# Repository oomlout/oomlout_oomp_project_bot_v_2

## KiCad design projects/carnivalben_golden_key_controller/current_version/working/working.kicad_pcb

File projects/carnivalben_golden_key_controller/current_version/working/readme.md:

# golden_key
 
## summary 
* id: carnivalben_golden_key_controller
* user: carnivalben
* name: golden_key
* board: controller
* repo: https://github.com/CarnivalBen/golden-key
* src_file_repo_kicad_pcb: controller/pcb/controller.kicad_pcb
* src_file_repo_kicad_pcb_link: https://github.com/CarnivalBen/golden-key/tree/master/controller/pcb/controller.kicad_pcb

* src_file_repo_sch: controller/pcb/controller.sch
* src_file_repo_sch_link: https://github.com/CarnivalBen/golden-key/tree/master/controller/pcb/controller.sch
* full details link: https://github.com/oomlout/oomlout_oomp_project_bot_v_2/tree/main/projects/carnivalben_golden_key_controller/current_version/working  

## schematic  
  
[schematic (pdf)](working_schematic.pdf) 

## pcb  

[board (pdf)](working.pdf)  

## working_bom
| Id | Designator | Footprint | Quantity | Designation | Supplier and ref |  | None | 
| --- | --- | --- | --- | --- | --- | --- | --- | 
| 1 | C5,C1,C3 | C_Disc_D3.0mm_W1.6mm_P2.50mm | 3 | 10nF |  |  | [''] | 
| 2 | D1,D17,D10,D12,D15 | LED_D5.0mm | 5 | WHITE |  |  | [''] | 
| 3 | D3 | LED_D5.0mm | 1 | W REV3 |  |  | [''] | 
| 4 | D4 | LED_D5.0mm | 1 | W REV2 |  |  | [''] | 
| 5 | D5 | LED_D5.0mm | 1 | W REV1 |  |  | [''] | 
| 6 | D6 | LED_D5.0mm | 1 | W FWD1 |  |  | [''] | 
| 7 | D7 | LED_D5.0mm | 1 | W FWD2 |  |  | [''] | 
| 8 | D8 | LED_D5.0mm | 1 | W FWD3 |  |  | [''] | 
| 9 | D9,D13,D14,D11 | D_A-405_P7.62mm_Horizontal | 4 | 1N4001 |  |  | [''] | 
| 10 | Q2,Q3 | TO-220-3_Horizontal | 2 | TIP32 |  |  | [''] | 
| 11 | Q4,Q5,Q15 | TO-92_Inline_Wide | 3 | 2N2222 |  |  | [''] | 
| 12 | Q12,Q13 | TO-220-3_Horizontal | 2 | TIP31 |  |  | [''] | 
| 13 | R2,R15,R16,R18,R19,R20,R27,R17 | R_Axial_DIN0411_L9.9mm_D3.6mm_P12.70mm_Horizontal | 8 | 330R |  |  | [''] | 
| 14 | R3,R1 | R_Axial_DIN0411_L9.9mm_D3.6mm_P12.70mm_Horizontal | 2 | 165R |  |  | [''] | 
| 15 | R11,R12 | R_Axial_DIN0411_L9.9mm_D3.6mm_P12.70mm_Horizontal | 2 | 100R |  |  | [''] | 
| 16 | R25 | R_Axial_DIN0411_L9.9mm_D3.6mm_P12.70mm_Horizontal | 1 | 1K |  |  | [''] | 
| 17 | U1 | TO-220-3_Horizontal | 1 | LM78M05 |  |  | [''] | 
| 18 | U2 | DIP-8_W7.62mm_Socket_LongPads | 1 | PIC12F1501-ISN |  |  | [''] | 
| 19 | U3 | DIP-16_W7.62mm_Socket_LongPads | 1 | 74HC595 |  |  | [''] | 
| 20 | D2 | D_A-405_P7.62mm_Horizontal | 1 | 12v |  |  | [''] | 
| 21 | D16 | LED_D5.0mm | 1 | W STOP |  |  | [''] | 
| 22 | J2 | Potentiometer_WirePads_Small | 1 | 10K POT |  |  | [''] | 
| 23 | C4,C2 | CP_Radial_D6.3mm_P2.50mm | 2 | 400uF |  |  | [''] | 
| 24 | J1 | Barrier_Terminal_P8.27_1x4 | 1 | POWER |  |  | [''] | 
| 25 | J3 | Pin_Header_Straight_1x03_Pitch2.54mm | 1 | Gradient |  |  | [''] | 

## bom_schematic
| Ref | Qnty | Value | Cmp name | Footprint | Description | Vendor | DNP | 
| --- | --- | --- | --- | --- | --- | --- | --- | 
| C1, C3, C5 | 3 | 10nF | C | Capacitors_THT:C_Disc_D3.0mm_W1.6mm_P2.50mm | Unpolarized capacitor |  |  | 
| C2, C4 | 2 | 400uF | CP-Device | Capacitors_THT:CP_Radial_D6.3mm_P2.50mm |  |  |  | 
| D1, D10, D12, D15, D17 | 5 | WHITE | LED | LEDs:LED_D5.0mm | Light emitting diode |  |  | 
| D2 | 1 | 12v | D_Zener | Diodes_THT:D_A-405_P7.62mm_Horizontal | Zener diode |  |  | 
| D3 | 1 | W REV3 | LED | LEDs:LED_D5.0mm | Light emitting diode |  |  | 
| D4 | 1 | W REV2 | LED | LEDs:LED_D5.0mm | Light emitting diode |  |  | 
| D5 | 1 | W REV1 | LED | LEDs:LED_D5.0mm | Light emitting diode |  |  | 
| D6 | 1 | W FWD1 | LED | LEDs:LED_D5.0mm | Light emitting diode |  |  | 
| D7 | 1 | W FWD2 | LED | LEDs:LED_D5.0mm | Light emitting diode |  |  | 
| D8 | 1 | W FWD3 | LED | LEDs:LED_D5.0mm | Light emitting diode |  |  | 
| D9, D11, D13, D14 | 4 | 1N4001 | D | Diodes_THT:D_A-405_P7.62mm_Horizontal | Diode |  |  | 
| D16 | 1 | W STOP | LED | LEDs:LED_D5.0mm | Light emitting diode |  |  | 
| J1 | 1 | POWER | Conn_01x04 | carnivalben:Barrier_Terminal_P8.27_1x4 | Generic connector, single row, 01x04, script generated (kicad-library-utils/schlib/autogen/connector/) |  |  | 
| J2 | 1 | 10K POT | Conn_01x03 | Potentiometers:Potentiometer_WirePads_Small | Generic connector, single row, 01x03, script generated (kicad-library-utils/schlib/autogen/connector/) |  |  | 
| J3 | 1 | Gradient | Conn_01x03 | Pin_Headers:Pin_Header_Straight_1x03_Pitch2.54mm | Generic connector, single row, 01x03, script generated (kicad-library-utils/schlib/autogen/connector/) |  |  | 
| Q2, Q3 | 2 | TIP32 | TIP42 | TO_SOT_Packages_THT:TO-220-3_Horizontal | -6A Ic, -40V Vce, Power PNP Transistor, TO-220 |  |  | 
| Q4, Q5, Q15 | 3 | 2N2222 | BC237 | TO_SOT_Packages_THT:TO-92_Inline_Wide | 100mA Ic, 50V Vce, Epitaxial Silicon NPN Transistor, TO-92 |  |  | 
| Q12, Q13 | 2 | TIP31 | TIP41 | TO_SOT_Packages_THT:TO-220-3_Horizontal | 6A Ic, 40V Vce, Power NPN Transistor, TO-220 |  |  | 
| R1, R3 | 2 | 165R | R | Resistors_THT:R_Axial_DIN0411_L9.9mm_D3.6mm_P12.70mm_Horizontal | Resistor |  |  | 
| R2, R15, R16, R17, R18, R19, R20, R27 | 8 | 330R | R | Resistors_THT:R_Axial_DIN0411_L9.9mm_D3.6mm_P12.70mm_Horizontal | Resistor |  |  | 
| R11, R12 | 2 | 100R | R | Resistors_THT:R_Axial_DIN0411_L9.9mm_D3.6mm_P12.70mm_Horizontal | Resistor |  |  | 
| R25 | 1 | 1K | R | Resistors_THT:R_Axial_DIN0411_L9.9mm_D3.6mm_P12.70mm_Horizontal | Resistor |  |  | 
| U1 | 1 | LM78M05_TO220 | LM78M05_TO220 | TO_SOT_Packages_THT:TO-220-3_Horizontal | Positive 500mA 35V Linear Regulator, Fixed Output 5V, TO-220 |  |  | 
| U2 | 1 | PIC12F1501-ISN | PIC12F1501-ISN | Housings_DIP:DIP-8_W7.62mm_Socket_LongPads | PIC12F1501, 1024W FLASH, 64B SRAM, SO8 |  |  | 
| U3 | 1 | 74HC595 | 74HC595 | Housings_DIP:DIP-16_W7.62mm_Socket_LongPads | 8-bit serial in/out Shift Register 3-State Outputs |  |  |

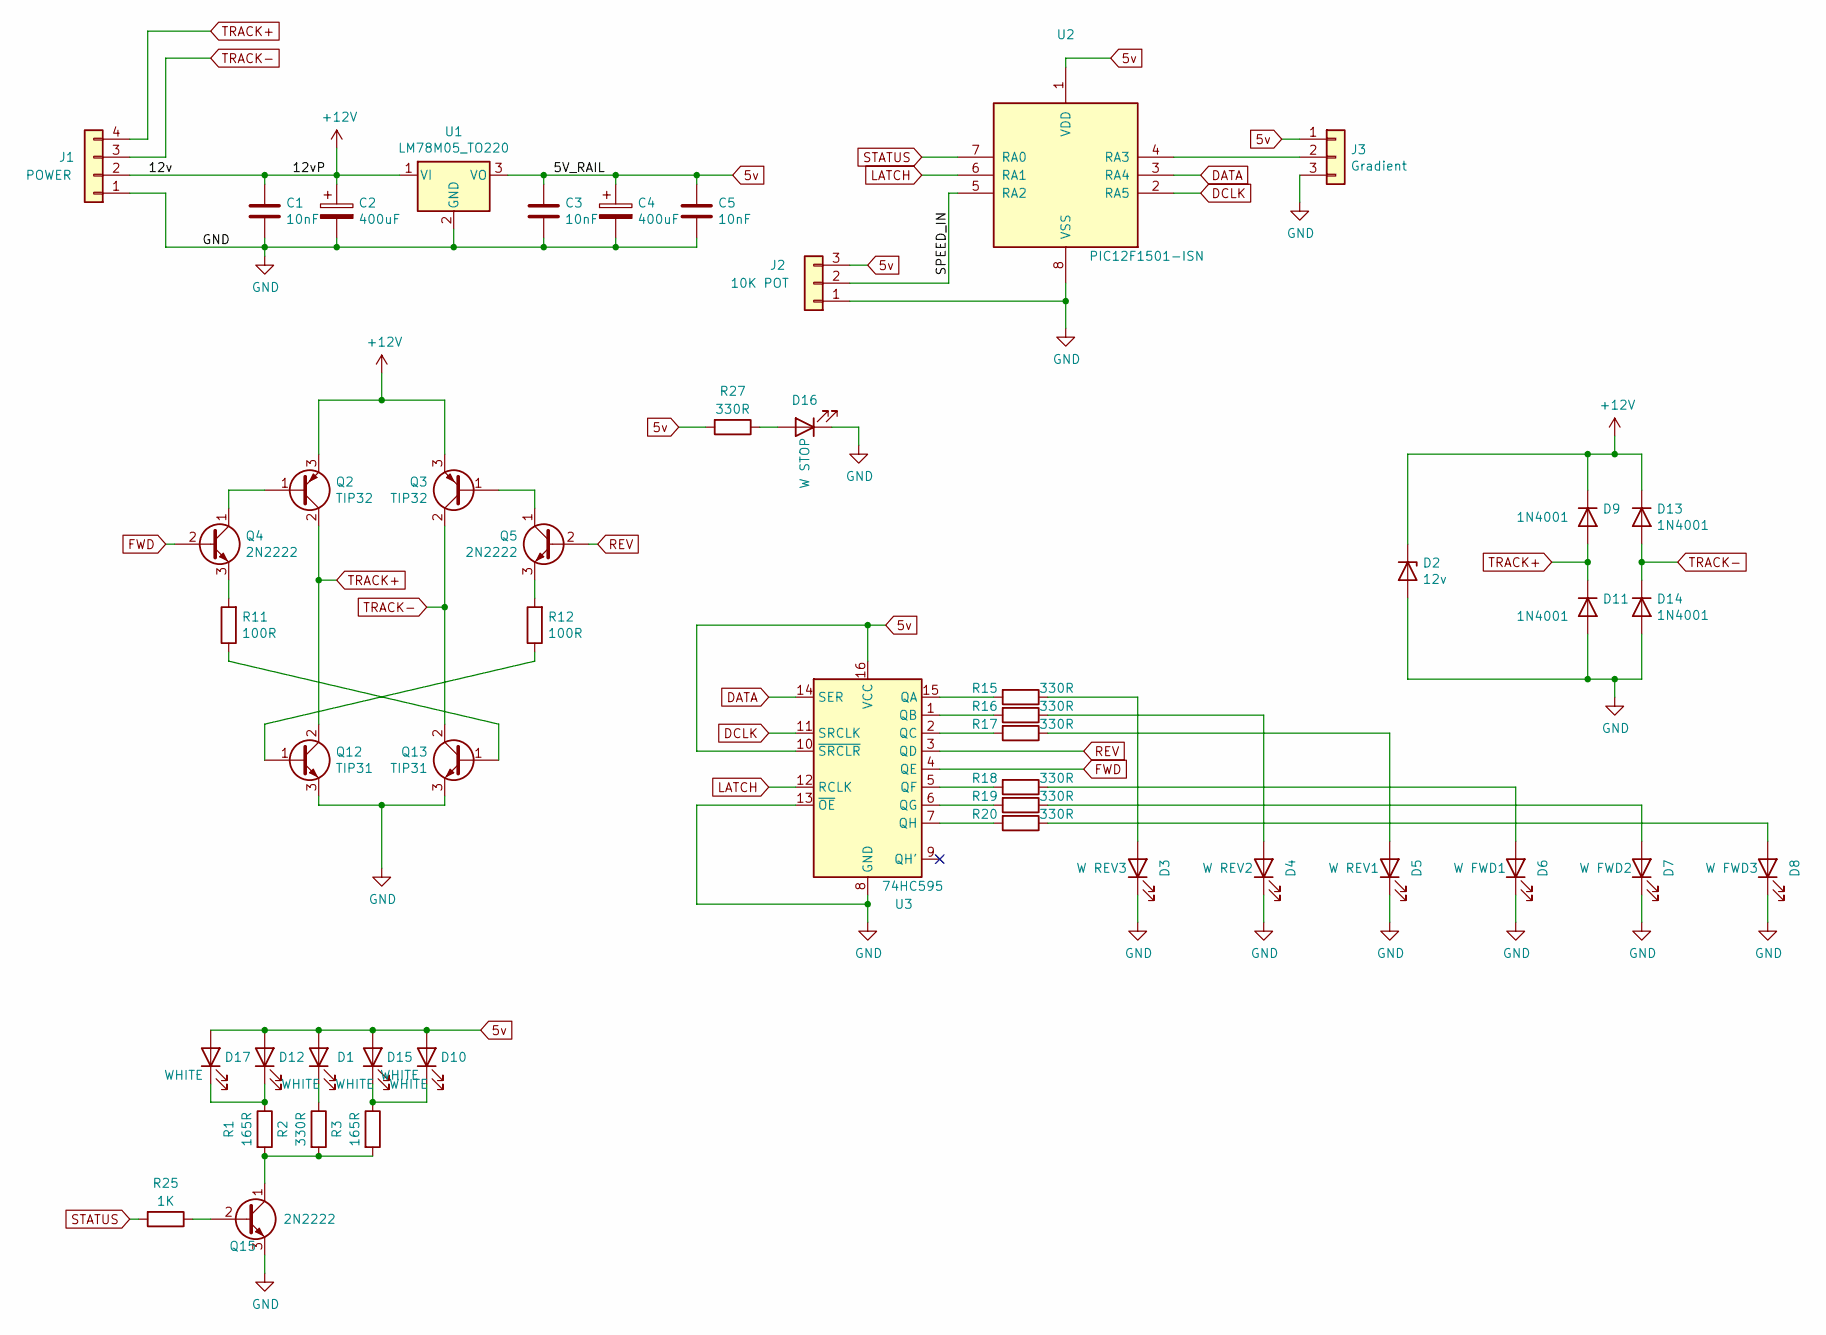
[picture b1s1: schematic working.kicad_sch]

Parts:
C1, C3, C5: 10nF; C_Disc_D3.0mm_W1.6mm_P2.50mm
C2, C4: 400uF; CP_Radial_D6.3mm_P2.50mm
D1, D10, D12, D15, D17: WHITE; LED_D5.0mm
D2: 12v; D_A-405_P7.62mm_Horizontal
D3: W REV3; LED_D5.0mm
D4: W REV2; LED_D5.0mm
D5: W REV1; LED_D5.0mm
D6: W FWD1; LED_D5.0mm
D7: W FWD2; LED_D5.0mm
D8: W FWD3; LED_D5.0mm
D9, D11, D13, D14: 1N4001; D_A-405_P7.62mm_Horizontal
D16: W STOP; LED_D5.0mm
J1: POWER; Barrier_Terminal_P8.27_1x4
J2: 10K POT; Potentiometer_WirePads_Small
J3: Gradient; Pin_Header_Straight_1x03_Pitch2.54mm
Q2, Q3: TIP32; TO-220-3_Horizontal
Q4, Q5, Q15: 2N2222; TO-92_Inline_Wide
Q12, Q13: TIP31; TO-220-3_Horizontal
R1, R3: 165R; R_Axial_DIN0411_L9.9mm_D3.6mm_P12.70mm_Horizontal
R2, R15, R16, R17, R18, R19, R20, R27: 330R; R_Axial_DIN0411_L9.9mm_D3.6mm_P12.70mm_Horizontal
R11, R12: 100R; R_Axial_DIN0411_L9.9mm_D3.6mm_P12.70mm_Horizontal
R25: 1K; R_Axial_DIN0411_L9.9mm_D3.6mm_P12.70mm_Horizontal
U1: LM78M05_TO220; TO-220-3_Horizontal
U2: PIC12F1501-ISN; DIP-8_W7.62mm_Socket_LongPads
U3: 74HC595; DIP-16_W7.62mm_Socket_LongPads

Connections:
5v: C3.1, C4.1, C5.1, D1.2 (A), D10.2 (A), D12.2 (A), D15.2 (A), D17.2 (A), J2.3, J3.1, R27.2, U1.3 (VO), U2.1 (VDD), U3.10 (~SRCLR), U3.16 (VCC)
+12V: C1.1, C2.1, D2.1 (K), D9.1 (K), D13.1 (K), J1.2, Q2.3 (E), Q3.3 (E), U1.1 (VI)
/SPEED_IN: J2.2, U2.5 (RA2)
DATA: U2.3 (RA4), U3.14 (SER)
DCLK: U2.2 (RA5), U3.11 (SRCLK)
FWD: Q4.2 (B), U3.4 (QE)
GND: C1.2, C2.2, C3.2, C4.2, C5.2, D2.2 (A), D3.1 (K), D4.1 (K), D5.1 (K), D6.1 (K), D7.1 (K), D8.1 (K), D11.2 (A), D14.2 (A), D16.1 (K), J1.1, J2.1, J3.3, Q12.3 (E), Q13.3 (E), Q15.3 (E), U1.2 (GND), U2.8 (VSS), U3.8 (GND), U3.13 (~OE)
LATCH: U2.6 (RA1), U3.12 (RCLK)
unnamed: D1.1 (K), R2.1
unnamed: D3.2 (A), R15.1
unnamed: D4.2 (A), R16.1
unnamed: D5.2 (A), R17.1
unnamed: D6.2 (A), R18.1
unnamed: D7.2 (A), R19.1
unnamed: D8.2 (A), R20.1
unnamed: D10.1 (K), D15.1 (K), R3.1
unnamed: D12.1 (K), D17.1 (K), R1.1
unnamed: D16.2 (A), R27.1
unnamed: J3.2, U2.4 (RA3)
unnamed: Q2.1 (B), Q4.1 (C)
unnamed: Q3.1 (B), Q5.1 (C)
unnamed: Q4.3 (E), R11.2
unnamed: Q5.3 (E), R12.2
unnamed: Q12.1 (B), R12.1
unnamed: Q13.1 (B), R11.1
unnamed: Q15.1 (C), R1.2, R2.2, R3.2
unnamed: Q15.2 (B), R25.1
unnamed: R15.2, U3.15 (QA)
unnamed: R16.2, U3.1 (QB)
unnamed: R17.2, U3.2 (QC)
unnamed: R18.2, U3.5 (QF)
unnamed: R19.2, U3.6 (QG)
unnamed: R20.2, U3.7 (QH)
REV: Q5.2 (B), U3.3 (QD)
STATUS: R25.2, U2.7 (RA0)
TRACK+: D9.2 (A), D11.1 (K), J1.4, Q2.2 (C), Q12.2 (C)
TRACK-: D13.2 (A), D14.1 (K), J1.3, Q3.2 (C), Q13.2 (C)

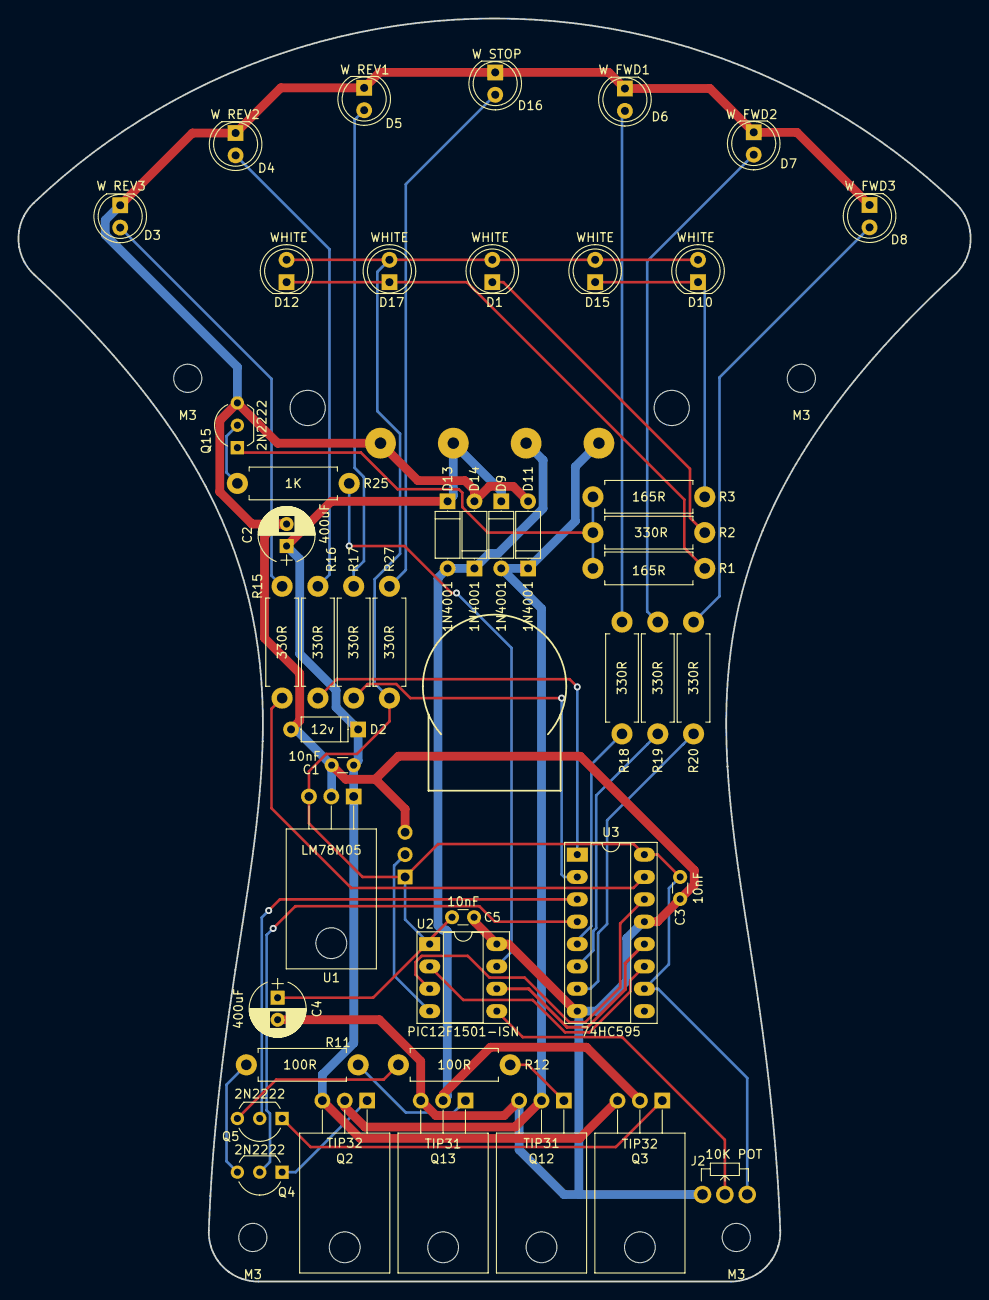
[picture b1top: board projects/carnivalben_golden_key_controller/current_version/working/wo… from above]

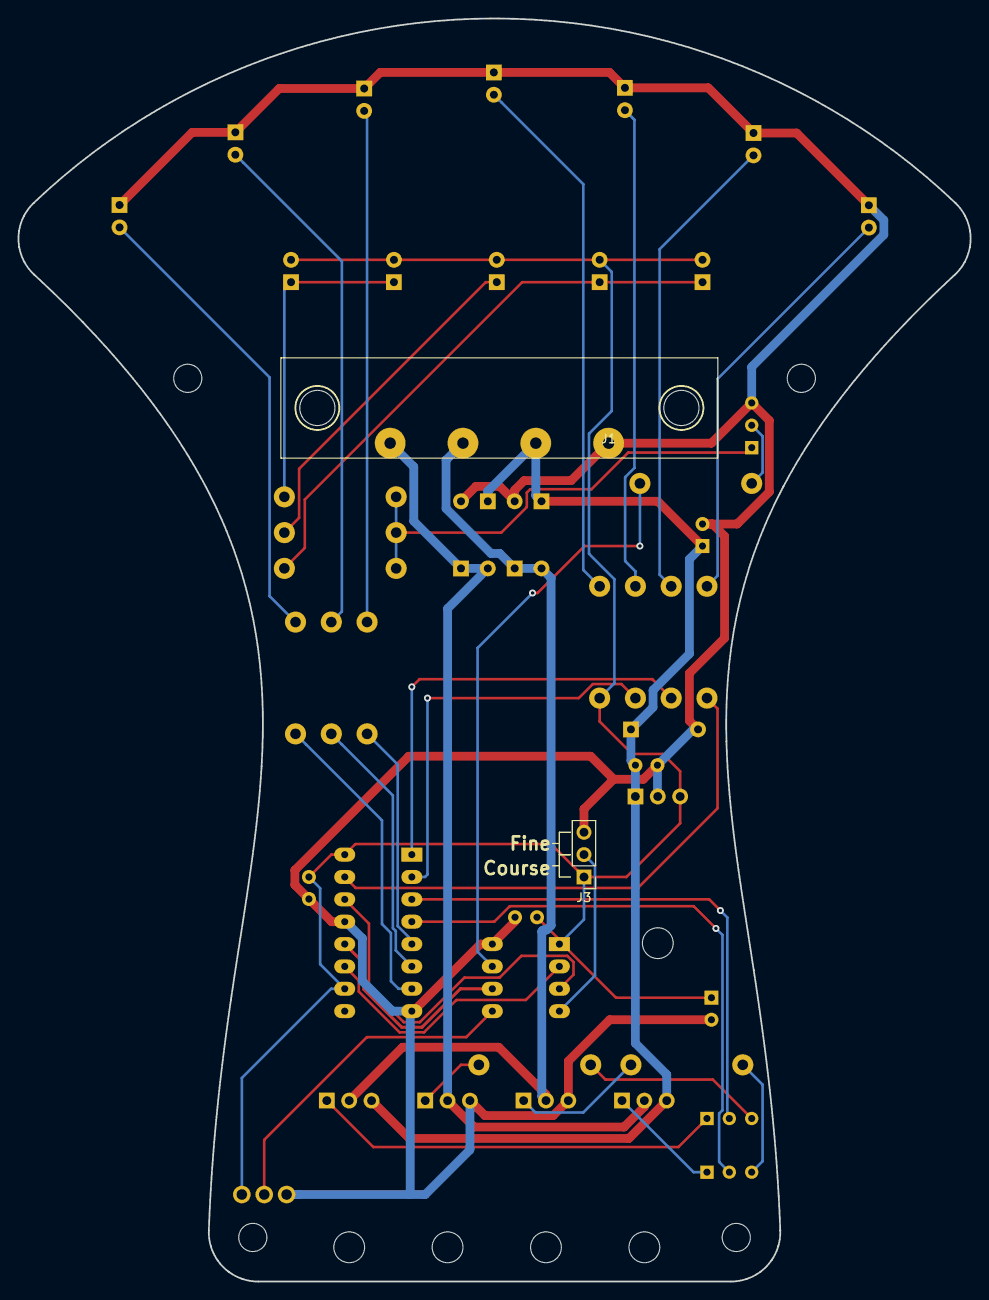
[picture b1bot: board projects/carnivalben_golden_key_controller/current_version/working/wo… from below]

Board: 2 copper layers, 108.1 x 143.5 mm, 48 parts (2 on the bottom side), 37 nets.

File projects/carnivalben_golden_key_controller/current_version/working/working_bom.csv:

"Id";"Designator";"Footprint";"Quantity";"Designation";"Supplier and ref";
1;"C5,C1,C3";"C_Disc_D3.0mm_W1.6mm_P2.50mm";3;"10nF";;;
2;"D1,D17,D10,D12,D15";"LED_D5.0mm";5;"WHITE";;;
3;"D3";"LED_D5.0mm";1;"W REV3";;;
4;"D4";"LED_D5.0mm";1;"W REV2";;;
5;"D5";"LED_D5.0mm";1;"W REV1";;;
6;"D6";"LED_D5.0mm";1;"W FWD1";;;
7;"D7";"LED_D5.0mm";1;"W FWD2";;;
8;"D8";"LED_D5.0mm";1;"W FWD3";;;
9;"D9,D13,D14,D11";"D_A-405_P7.62mm_Horizontal";4;"1N4001";;;
10;"Q2,Q3";"TO-220-3_Horizontal";2;"TIP32";;;
11;"Q4,Q5,Q15";"TO-92_Inline_Wide";3;"2N2222";;;
12;"Q12,Q13";"TO-220-3_Horizontal";2;"TIP31";;;
13;"R2,R15,R16,R18,R19,R20,R27,R17";"R_Axial_DIN0411_L9.9mm_D3.6mm_P12.70mm_Horizontal";8;"330R";;;
14;"R3,R1";"R_Axial_DIN0411_L9.9mm_D3.6mm_P12.70mm_Horizontal";2;"165R";;;
15;"R11,R12";"R_Axial_DIN0411_L9.9mm_D3.6mm_P12.70mm_Horizontal";2;"100R";;;
16;"R25";"R_Axial_DIN0411_L9.9mm_D3.6mm_P12.70mm_Horizontal";1;"1K";;;
17;"U1";"TO-220-3_Horizontal";1;"LM78M05";;;
18;"U2";"DIP-8_W7.62mm_Socket_LongPads";1;"PIC12F1501-ISN";;;
19;"U3";"DIP-16_W7.62mm_Socket_LongPads";1;"74HC595";;;
20;"D2";"D_A-405_P7.62mm_Horizontal";1;"12v";;;
21;"D16";"LED_D5.0mm";1;"W STOP";;;
22;"J2";"Potentiometer_WirePads_Small";1;"10K POT";;;
23;"C4,C2";"CP_Radial_D6.3mm_P2.50mm";2;"400uF";;;
24;"J1";"Barrier_Terminal_P8.27_1x4";1;"POWER";;;
25;"J3";"Pin_Header_Straight_1x03_Pitch2.54mm";1;"Gradient";;;

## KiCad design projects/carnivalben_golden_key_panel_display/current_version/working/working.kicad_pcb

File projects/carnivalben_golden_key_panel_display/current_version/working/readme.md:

# golden_key
 
## summary 
* id: carnivalben_golden_key_panel_display
* user: carnivalben
* name: golden_key
* board: panel_display
* repo: https://github.com/CarnivalBen/golden-key
* src_file_repo_kicad_pcb: panel/pcb-display/panel-display - Copy.kicad_pcb
* src_file_repo_kicad_pcb_link: https://github.com/CarnivalBen/golden-key/tree/master/panel/pcb-display/panel-display - Copy.kicad_pcb

* src_file_repo_sch: layout-diag/layout-diag.sch
* src_file_repo_sch_link: https://github.com/CarnivalBen/golden-key/tree/master/layout-diag/layout-diag.sch
* full details link: https://github.com/oomlout/oomlout_oomp_project_bot_v_2/tree/main/projects/carnivalben_golden_key_panel_display/current_version/working  

## pcb  

[board (pdf)](working.pdf)  

## working_bom
| Id | Designator | Footprint | Quantity | Designation | Supplier and ref |  | None | 
| --- | --- | --- | --- | --- | --- | --- | --- | 
| 1 | C5,C6,C1,C2,C3,C4 | C_Disc_D3.0mm_W1.6mm_P2.50mm | 6 | 10nF |  |  | [''] | 
| 2 | J1 | Pin_Header_Straight_2x06_Pitch2.54mm | 1 | PUSH-BUTTON |  |  | [''] | 
| 3 | SW5 | SW_PUSH_6mm_4pin | 1 | BUTTON B |  |  | [''] | 
| 4 | SW6 | SW_PUSH_6mm_4pin | 1 | BUTTON C |  |  | [''] | 
| 5 | SW9 | SW_PUSH_6mm_4pin | 1 | BUTTON H |  |  | [''] | 
| 6 | SW7 | SW_PUSH_6mm_4pin | 1 | BUTTON G |  |  | [''] | 
| 7 | SW8 | SW_PUSH_6mm_4pin | 1 | BUTTON D |  |  | [''] | 
| 8 | SW10 | SW_PUSH_6mm_4pin | 1 | BUTTON E |  |  | [''] | 
| 9 | SW3 | SW_PUSH_6mm_4pin | 1 | BUTTON A |  |  | [''] | 
| 10 | SW4 | SW_PUSH_6mm_4pin | 1 | BUTTON F |  |  | [''] | 
| 11 | SW2 | SW_PUSH_6mm_4pin | 1 | BUTTON J |  |  | [''] | 
| 12 | SW1 | SW_PUSH_6mm_4pin | 1 | BUTTON I |  |  | [''] | 
| 13 | D9,D7,D4,D3,D5,D8,D6 | LED_D5.0mm | 7 | WHITE |  |  | [''] | 
| 14 | J2 | Pin_Header_Straight_2x06_Pitch2.54mm | 1 | POWER |  |  | [''] | 
| 15 | D2,D1 | LED_D5.0mm | 2 | YELLOW |  |  | [''] | 
| 16 | D39,D73,D99,D128,D10,D11,D12,D16,D17,D18,D19,D20,D26,D27,D28,D32,D33,D34,D38,D40,D44,D45,D46,D47,D48,D56,D57,D58,D59,D60,D62,D72,D74,D75,D76,D77,D84,D85,D86,D87,D90,D91,D92,D93,D98,D100,D101,D107,D108,D109,D110,D114,D115,D116,D121,D122,D125,D127,D129,D130,D131,D139,D140,D141,D142,D117,D22 | LED_D5.0mm | 67 | GREEN |  |  | [''] | 
| 17 | U7,U8,U9,U13,U1,U2,U3 | DIP-16_W7.62mm_LongPads | 7 | ULN2003A |  |  | [''] | 
| 18 | U10,U11,U12,U4,U5,U6 | DIP-16_W7.62mm_LongPads | 6 | 74HC595 |  |  | [''] | 
| 19 | D13,D14,D15,D21,D23,D24,D25,D29,D30,D31,D35,D36,D37,D41,D43,D50,D51,D52,D53,D54,D55,D61,D63,D64,D66,D67,D68,D69,D70,D71,D78,D79,D80,D81,D82,D83,D88,D89,D94,D95,D96,D97,D102,D103,D104,D105,D106,D111,D112,D113,D118,D119,D120,D123,D124,D132,D133,D134,D135,D136,D137,D144,D65 | LED_D5.0mm | 63 | RED |  |  | [''] | 
| 20 | Q1,Q2 | TO-92_Inline_Wide | 2 | 2N2222 |  |  | [''] | 
| 21 | R1,R2,R3,R4,R5,R6,R7,R8,R9,R10,R13,R14 | R_Axial_DIN0207_L6.3mm_D2.5mm_P10.16mm_Horizontal | 12 | 10K |  |  | [''] | 
| 22 | R11,R12,R19,R20,R21,R22,R23,R24,R25,R26,R27,R28,R29,R30,R31,R32,R33,R34,R35,R36,R37,R38,R39,R40,R41,R42,R43,R44,R45,R46,R47,R48,R49,R50,R51,R52,R53,R54,R55,R56,R57,R58,R59,R60,R61,R62,R63,R64,R65,R66,R67,R68 | R_Axial_DIN0207_L6.3mm_D2.5mm_P10.16mm_Horizontal | 52 | 4.7K |  |  | [''] | 
| 23 | R15,R16,R17,R18 | R_Axial_DIN0207_L6.3mm_D2.5mm_P10.16mm_Horizontal | 4 | 400R |  |  | [''] |

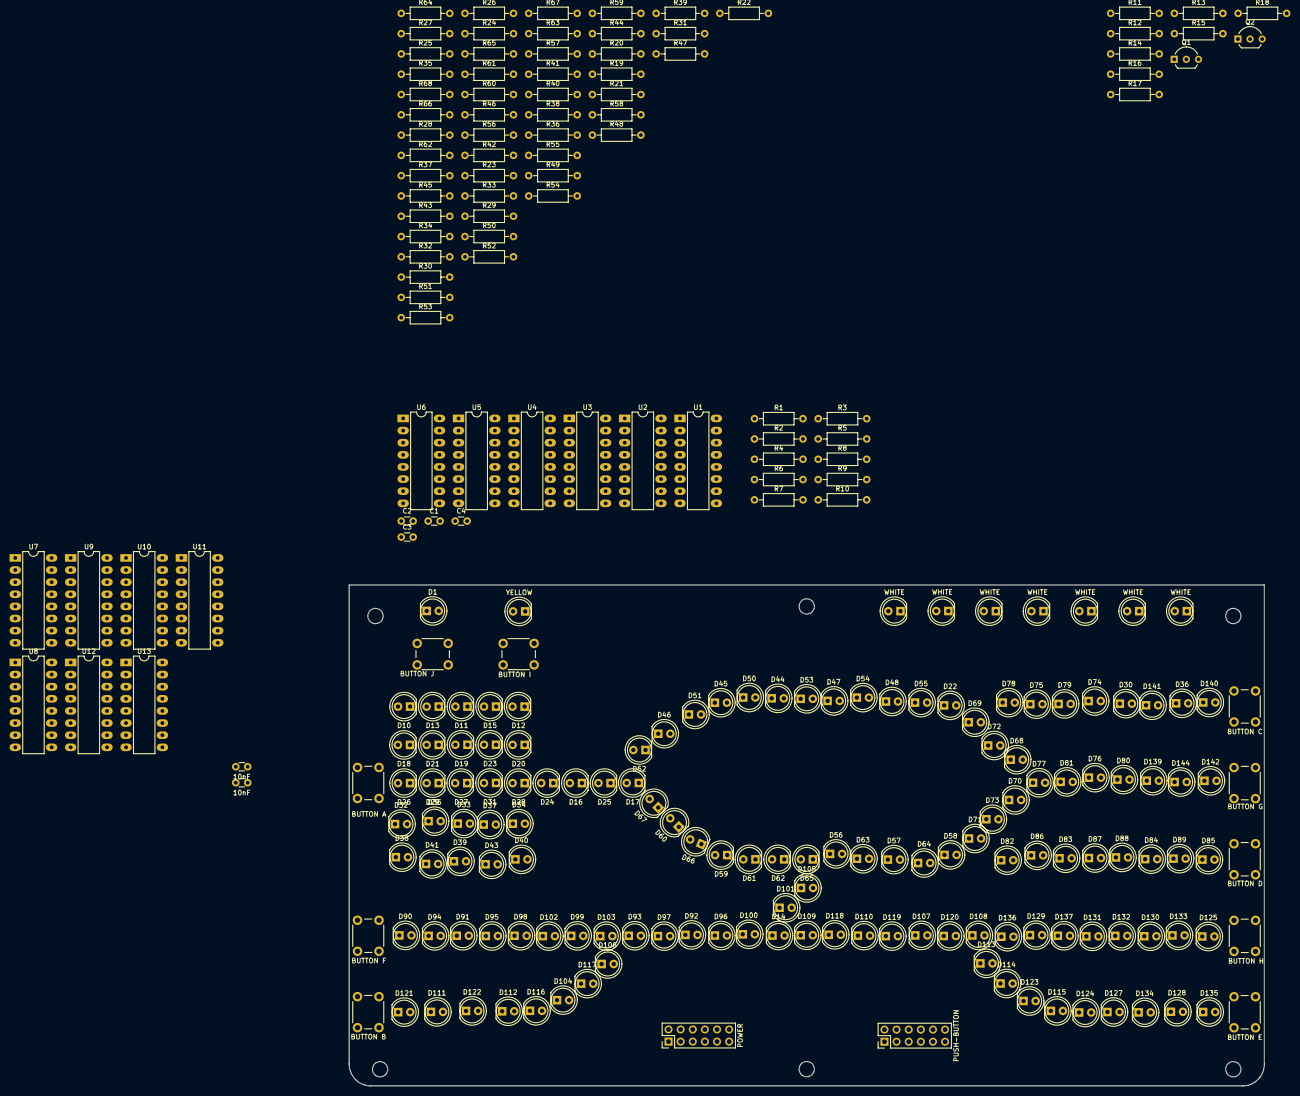
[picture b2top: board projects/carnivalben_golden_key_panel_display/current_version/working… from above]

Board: 2 copper layers, 191.7 x 104.9 mm, 240 parts (0 on the bottom side), 263 nets, no tracks yet.

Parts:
C1, C2, C3, C4, C5, C6: 10nF; C_Disc_D3.0mm_W1.6mm_P2.50mm
D1, D2: YELLOW; LED_D5.0mm
D3, D4, D5, D6, D7, D8, D9: WHITE; LED_D5.0mm
D10, D11, D12, D16, D17, D18, D19, D20, D22, D26, D27, D28, D32, D33, D34, D38, D39, D40, D44, D45, D46, D47, D48, D56, D57, D58, D59, D60, D62, D72, D73, D74, D75, D76, D77, D84, D85, D86, D87, D90, D91, D92, D93, D98, D99, D100, D101, D107, D108, D109, D110, D114, D115, D116, D117, D121, D122, D125, D127, D128, D129, D130, D131, D139, D140, D141, D142: GREEN; LED_D5.0mm
D13, D14, D15, D21, D23, D24, D25, D29, D30, D31, D35, D36, D37, D41, D43, D50, D51, D52, D53, D54, D55, D61, D63, D64, D65, D66, D67, D68, D69, D70, D71, D78, D79, D80, D81, D82, D83, D88, D89, D94, D95, D96, D97, D102, D103, D104, D105, D106, D111, D112, D113, D118, D119, D120, D123, D124, D132, D133, D134, D135, D136, D137, D144: RED; LED_D5.0mm
J1: PUSH-BUTTON; Pin_Header_Straight_2x06_Pitch2.54mm
J2: POWER; Pin_Header_Straight_2x06_Pitch2.54mm
Q1, Q2: 2N2222; TO-92_Inline_Wide
R1, R2, R3, R4, R5, R6, R7, R8, R9, R10, R13, R14: 10K; R_Axial_DIN0207_L6.3mm_D2.5mm_P10.16mm_Horizontal
R11, R12, R19, R20, R21, R22, R23, R24, R25, R26, R27, R28, R29, R30, R31, R32, R33, R34, R35, R36, R37, R38, R39, R40, R41, R42, R43, R44, R45, R46, R47, R48, R49, R50, R51, R52, R53, R54, R55, R56, R57, R58, R59, R60, R61, R62, R63, R64, R65, R66, R67, R68: 4.7K; R_Axial_DIN0207_L6.3mm_D2.5mm_P10.16mm_Horizontal
R15, R16, R17, R18: 400R; R_Axial_DIN0207_L6.3mm_D2.5mm_P10.16mm_Horizontal
SW1: BUTTON I; SW_PUSH_6mm_4pin
SW2: BUTTON J; SW_PUSH_6mm_4pin
SW3: BUTTON A; SW_PUSH_6mm_4pin
SW4: BUTTON F; SW_PUSH_6mm_4pin
SW5: BUTTON B; SW_PUSH_6mm_4pin
SW6: BUTTON C; SW_PUSH_6mm_4pin
SW7: BUTTON G; SW_PUSH_6mm_4pin
SW8: BUTTON D; SW_PUSH_6mm_4pin
SW9: BUTTON H; SW_PUSH_6mm_4pin
SW10: BUTTON E; SW_PUSH_6mm_4pin
U1, U2, U3, U7, U8, U9, U13: ULN2003A; DIP-16_W7.62mm_LongPads
U4, U5, U6, U10, U11, U12: 74HC595; DIP-16_W7.62mm_LongPads

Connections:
+5V: C1.2, C2.2, C3.2, C4.2, C5.2, C6.2, J2.12, SW1.1, SW1.3, SW2.1, SW2.3, SW3.1, SW3.3, SW4.1, SW4.3, SW5.1, SW5.3, SW6.1, SW6.3, SW7.1, SW7.3, SW8.1, SW8.3, SW9.1, SW9.3, SW10.1, SW10.3, U4.16, U5.16, U6.16, U10.16, U11.16, U12.16
+12P: D1.2, D2.2, J2.1, R17.1, R18.1, R19.1, R20.1, R21.1, R22.1, R23.1, R24.1, R25.1, R26.1, R27.1, R28.1, R29.1, R30.1, R31.1, R32.1, R33.1, R34.1, R35.1, R36.1, R37.1, R38.1, R39.1, R40.1, R41.1, R42.1, R43.1, R44.1, R45.1, R46.1, R47.1, R48.1, R49.1, R50.1, R51.1, R52.1, R53.1, R54.1, R55.1, R56.1, R57.1, R58.1, R59.1, R60.1, R61.1, R62.1, R63.1, R64.1, R65.1, R66.1, R67.1, R68.1
/LED1: D121.1, U1.16
/LED2: D125.1, U2.13
/LED3: D108.1, U2.11
/LED4: D128.1, U3.14
/LED5: D115.1, U3.16
/LED6: D12.1, U13.12
/LED7: D20.1, U13.14
/LED8: D28.1, U13.16
/LED9: D34.1, U7.11
/LED10: D40.1, U7.13
/LED11: D17.1, U7.15
/LED12: D22.1, D44.1, U8.10
/LED13: D72.1, U9.11
/LED14: D73.1, U8.16
/LED15: D58.1, U8.14
/LED16: D62.1, U8.12
/LED17: D140.1, U9.13
/LED18: D142.1, U9.15
/LED19: D87.1, U3.10
/LED20: D85.1, U3.12
/LED21: D90.1, U1.14
/LED22: D98.1, U1.12
/LED23: D93.1, U1.10
/LED24: D101.1, U2.15
/LED25: D111.1, U1.15
/LED26: D133.1, U2.12
/LED27: D120.1, U2.10
/LED28: D135.1, U3.13
/LED29: D124.1, U3.15
/LED30: D15.1, U13.11
/LED31: D23.1, U13.13
/LED32: D31.1, U13.15
/LED33: D37.1, U7.10
/LED34: D43.1, U7.12
/LED35: D25.1, U7.14
/LED36: D50.1, D55.1, U7.16
/LED37: D68.1, U9.10
/LED38: D70.1, U8.15
/LED39: D64.1, U8.13
/LED40: D65.1, U8.11
/LED41: D36.1, U9.12
/LED42: D144.1, U9.14
/LED43: D83.1, U9.16
/LED44: D89.1, U3.11
/LED45: D94.1, U1.13
/LED46: D102.1, U1.11
/LED47: D97.1, U2.16
/LED48: D105.1, U2.14
/LED Aux/AUX1: J2.11, R11.1, R13.1
/LED Aux/AUX2: J2.10, R12.1, R14.1
/Panel Display Buttons/PB-AUX1: J1.1, R1.2, SW1.2, SW1.4
/Panel Display Buttons/PB-AUX2: J1.2, R2.2, SW2.2, SW2.4
/Panel Display Buttons/PB-DK: J1.5, R9.2, SW9.2, SW9.4
/Panel Display Buttons/PB-FY: J1.3, R4.2, SW4.2, SW4.4
/Panel Display Buttons/PB-GS: J1.12, R3.2, SW3.2, SW3.4
/Panel Display Buttons/PB-MLE: J1.9, R8.2, SW8.2, SW8.4
/Panel Display Buttons/PB-MLW: J1.4, R7.2, SW7.2, SW7.4
/Panel Display Buttons/PB-PL1: J1.11, R5.2, SW5.2, SW5.4
/Panel Display Buttons/PB-PL2: J1.10, R6.2, SW6.2, SW6.4
/Panel Display Buttons/PB-SD: J1.8, R10.2, SW10.2, SW10.4
DATA: J2.2, U4.14
DCLK: J2.3, U4.11, U5.11, U6.11, U10.11, U11.11, U12.11
DLAT: J2.5, U4.12, U5.12, U6.12, U10.12, U11.12, U12.12
EX1: U4.7, U13.1
EX2: U5.7, U13.2
EX3: U6.7, U13.3
EX4: U10.7, U13.4
EX5: U11.7, U13.5
EX6: U12.7, U13.6
GND: C1.1, C2.1, C3.1, C4.1, C5.1, C6.1, D6.1, D9.1, J2.8, Q1.3, Q2.3, R1.1, R2.1, R3.1, R4.1, R5.1, R6.1, R7.1, R8.1, R9.1, R10.1, R13.2, R14.2, U1.8, U2.8, U3.8, U4.8, U4.13, U5.8, U5.13, U6.8, U6.13, U7.8, U8.8, U9.8, U10.8, U10.13, U11.8, U11.13, U12.8, U12.13, U13.8
unnamed: D1.1, R15.1
unnamed: D2.1, R16.1
unnamed: D3.1, D4.2
unnamed: D3.2, R17.2
unnamed: D4.1, D5.2
unnamed: D5.1, D6.2
unnamed: D7.1, D8.2
unnamed: D7.2, R18.2
unnamed: D8.1, D9.2
unnamed: D10.1, D11.2
unnamed: D10.2, R24.2
unnamed: D11.1, D12.2
unnamed: D13.1, D15.2
unnamed: D13.2, R47.2
unnamed: D14.1, D96.2
unnamed: D14.2, R63.2
unnamed: D16.1, D17.2
unnamed: D16.2, R29.2
unnamed: D18.1, D19.2
unnamed: D18.2, R25.2
unnamed: D19.1, D20.2
unnamed: D21.1, D23.2
unnamed: D21.2, R48.2
unnamed: D22.2, D48.1
unnamed: D24.1, D25.2
unnamed: D24.2, R52.2
unnamed: D26.1, D27.2
unnamed: D26.2, R26.2
unnamed: D27.1, D28.2
unnamed: D29.1, D31.2
unnamed: D29.2, R49.2
unnamed: D30.1, D36.2
unnamed: D30.2, D79.1
unnamed: D32.1, D33.2
unnamed: D32.2, R27.2
unnamed: D33.1, D34.2
unnamed: D35.1, D37.2
unnamed: D35.2, R50.2
unnamed: D38.1, D39.2
unnamed: D38.2, R28.2
unnamed: D39.1, D40.2
unnamed: D41.1, D43.2
unnamed: D41.2, R51.2
unnamed: D44.2, D45.1
unnamed: D45.2, D46.1
unnamed: D46.2, R65.2
unnamed: D47.1, D48.2
unnamed: D47.2, R67.2
unnamed: D50.2, D51.1
unnamed: D51.2, D52.1
unnamed: D52.2, R66.2
unnamed: D53.1, D54.2
unnamed: D53.2, R68.2
unnamed: D54.1, D55.2
unnamed: D56.1, D57.2
unnamed: D56.2, R32.2
unnamed: D57.1, D58.2
unnamed: D59.1, D62.2
unnamed: D59.2, D60.1
unnamed: D60.2, R33.2
unnamed: D61.1, D65.2
unnamed: D61.2, D66.1
unnamed: D63.1, D64.2
unnamed: D63.2, R55.2
unnamed: D66.2, D67.1
unnamed: D67.2, R56.2
unnamed: D68.2, D69.1
unnamed: D69.2, R53.2
unnamed: D70.2, D71.1
unnamed: D71.2, R54.2
unnamed: D72.2, R30.2
unnamed: D73.2, R31.2
unnamed: D74.2, D75.1
unnamed: D75.2, R34.2
unnamed: D76.2, D77.1
unnamed: D77.2, R35.2
unnamed: D78.1, D79.2
unnamed: D78.2, R57.2
unnamed: D80.2, D81.1
unnamed: D81.2, R58.2
unnamed: D82.1, D83.2
unnamed: D82.2, R59.2
unnamed: D84.1, D85.2
unnamed: D84.2, R37.2
unnamed: D86.1, D87.2
unnamed: D86.2, R36.2
unnamed: D88.1, D89.2
unnamed: D88.2, R60.2
unnamed: D90.2, D91.1
unnamed: D91.2, R38.2
unnamed: D92.1, D93.2
unnamed: D94.2, D95.1
unnamed: D95.2, R61.2
unnamed: D96.1, D97.2
unnamed: D98.2, D99.1
unnamed: D99.2, R39.2
unnamed: D92.2, D100.1
unnamed: D100.2, R40.2
unnamed: D101.2, R41.2
unnamed: D102.2, D103.1
unnamed: D103.2, R62.2
unnamed: D104.1, D112.2
unnamed: D104.2, D106.1
unnamed: D105.2, R64.2
unnamed: D106.2, R42.2
unnamed: D107.1, D108.2
unnamed: D107.2, D110.1
unnamed: D109.1, D110.2
unnamed: D109.2, R21.2
unnamed: D111.2, D112.1
unnamed: D113.1, D123.2
unnamed: D113.2, R46.2
unnamed: D114.1, D115.2
unnamed: D114.2, R23.2
unnamed: D116.1, D122.2
unnamed: D116.2, D117.1
unnamed: D117.2, R19.2
unnamed: D118.1, D119.2
unnamed: D118.2, R44.2
unnamed: D119.1, D120.2
unnamed: D121.2, D122.1
unnamed: D123.1, D124.2
unnamed: D125.2, D130.1
unnamed: D127.1, D128.2
unnamed: D127.2, R22.2
unnamed: D129.1, D131.2
unnamed: D129.2, R20.2
unnamed: D130.2, D131.1
unnamed: D132.1, D133.2
unnamed: D132.2, D137.1
unnamed: D134.1, D135.2
unnamed: D134.2, R45.2
unnamed: D136.1, D137.2
unnamed: D136.2, R43.2
unnamed: D139.1, D142.2
unnamed: D76.1, D139.2
unnamed: D140.2, D141.1
unnamed: D74.1, D141.2
unnamed: D80.1, D144.2
unnamed: Q1.1, R15.2
unnamed: Q1.2, R11.2
unnamed: Q2.1, R16.2
unnamed: Q2.2, R12.2
unnamed: U1.1, U4.15
unnamed: U1.2, U4.1
unnamed: U1.3, U4.2
unnamed: U1.4, U4.3
unnamed: U1.5, U4.4
unnamed: U1.6, U4.5
unnamed: U1.7, U4.6
unnamed: U2.1, U5.15
unnamed: U2.2, U5.1
unnamed: U2.3, U5.2
unnamed: U2.4, U5.3
unnamed: U2.5, U5.4
unnamed: U2.6, U5.5
unnamed: U2.7, U5.6
unnamed: U3.1, U6.15
unnamed: U3.2, U6.1
unnamed: U3.3, U6.2
unnamed: U3.4, U6.3
unnamed: U3.5, U6.4
unnamed: U3.6, U6.5
unnamed: U3.7, U6.6
unnamed: U4.9, U5.14
unnamed: U5.9, U6.14
unnamed: U7.2, U10.1
unnamed: U7.3, U10.2
unnamed: U7.4, U10.3
unnamed: U7.5, U10.4
unnamed: U7.6, U10.5
unnamed: U7.7, U10.6
unnamed: U10.9, U11.14
unnamed: U6.9, U10.14
unnamed: U7.1, U10.15
unnamed: U8.2, U11.1
unnamed: U8.3, U11.2
unnamed: U8.4, U11.3
unnamed: U8.5, U11.4
unnamed: U8.6, U11.5
unnamed: U8.7, U11.6
unnamed: U11.9, U12.14
unnamed: U8.1, U11.15
unnamed: U9.2, U12.1
unnamed: U9.3, U12.2
unnamed: U9.4, U12.3
unnamed: U9.5, U12.4
unnamed: U9.6, U12.5
unnamed: U9.7, U12.6
unnamed: U9.1, U12.15
RST: J2.4, U4.10, U5.10, U6.10, U10.10, U11.10, U12.10

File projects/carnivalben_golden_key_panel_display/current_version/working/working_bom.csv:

"Id";"Designator";"Footprint";"Quantity";"Designation";"Supplier and ref";
1;"C5,C6,C1,C2,C3,C4";"C_Disc_D3.0mm_W1.6mm_P2.50mm";6;"10nF";;;
2;"J1";"Pin_Header_Straight_2x06_Pitch2.54mm";1;"PUSH-BUTTON";;;
3;"SW5";"SW_PUSH_6mm_4pin";1;"BUTTON B";;;
4;"SW6";"SW_PUSH_6mm_4pin";1;"BUTTON C";;;
5;"SW9";"SW_PUSH_6mm_4pin";1;"BUTTON H";;;
6;"SW7";"SW_PUSH_6mm_4pin";1;"BUTTON G";;;
7;"SW8";"SW_PUSH_6mm_4pin";1;"BUTTON D";;;
8;"SW10";"SW_PUSH_6mm_4pin";1;"BUTTON E";;;
9;"SW3";"SW_PUSH_6mm_4pin";1;"BUTTON A";;;
10;"SW4";"SW_PUSH_6mm_4pin";1;"BUTTON F";;;
11;"SW2";"SW_PUSH_6mm_4pin";1;"BUTTON J";;;
12;"SW1";"SW_PUSH_6mm_4pin";1;"BUTTON I";;;
13;"D9,D7,D4,D3,D5,D8,D6";"LED_D5.0mm";7;"WHITE";;;
14;"J2";"Pin_Header_Straight_2x06_Pitch2.54mm";1;"POWER";;;
15;"D2,D1";"LED_D5.0mm";2;"YELLOW";;;
16;"D39,D73,D99,D128,D10,D11,D12,D16,D17,D18,D19,D20,D26,D27,D28,D32,D33,D34,D38,D40,D44,D45,D46,D47,D48,D56,D57,D58,D59,D60,D62,D72,D74,D75,D76,D77,D84,D85,D86,D87,D90,D91,D92,D93,D98,D100,D101,D107,D108,D109,D110,D114,D115,D116,D121,D122,D125,D127,D129,D130,D131,D139,D140,D141,D142,D117,D22";"LED_D5.0mm";67;"GREEN";;;
17;"U7,U8,U9,U13,U1,U2,U3";"DIP-16_W7.62mm_LongPads";7;"ULN2003A";;;
18;"U10,U11,U12,U4,U5,U6";"DIP-16_W7.62mm_LongPads";6;"74HC595";;;
19;"D13,D14,D15,D21,D23,D24,D25,D29,D30,D31,D35,D36,D37,D41,D43,D50,D51,D52,D53,D54,D55,D61,D63,D64,D66,D67,D68,D69,D70,D71,D78,D79,D80,D81,D82,D83,D88,D89,D94,D95,D96,D97,D102,D103,D104,D105,D106,D111,D112,D113,D118,D119,D120,D123,D124,D132,D133,D134,D135,D136,D137,D144,D65";"LED_D5.0mm";63;"RED";;;
20;"Q1,Q2";"TO-92_Inline_Wide";2;"2N2222";;;
21;"R1,R2,R3,R4,R5,R6,R7,R8,R9,R10,R13,R14";"R_Axial_DIN0207_L6.3mm_D2.5mm_P10.16mm_Horizontal";12;"10K";;;
22;"R11,R12,R19,R20,R21,R22,R23,R24,R25,R26,R27,R28,R29,R30,R31,R32,R33,R34,R35,R36,R37,R38,R39,R40,R41,R42,R43,R44,R45,R46,R47,R48,R49,R50,R51,R52,R53,R54,R55,R56,R57,R58,R59,R60,R61,R62,R63,R64,R65,R66,R67,R68";"R_Axial_DIN0207_L6.3mm_D2.5mm_P10.16mm_Horizontal";52;"4.7K";;;
23;"R15,R16,R17,R18";"R_Axial_DIN0207_L6.3mm_D2.5mm_P10.16mm_Horizontal";4;"400R";;;
